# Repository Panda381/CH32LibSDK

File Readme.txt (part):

CH32LibSDK - SDK library for low-end CH32 RISC-V microcontrollers
=================================================================
Pre-alpha version 0.39, under development.

Copyright (c) 2025 Miroslav Nemecek

Panda38@seznam.cz
hardyplotter2@gmail.com
https://github.com/Panda381/CH32LibSDK
https://www.breatharian.eu/hw/ch32libsdk/index_en.html

How to compile on Windows, using command line:

- Use FAR Manager to edit source files and run BAT scripts.
- Download MounRiver Studio v1.92 http://mounriver.com/download
- Install MounRiver Studio. 
- Extract "toolchain\RISC-V Embedded GCC12" compiler to separate folder.
- Edit _c1.bat file and enter path to "bin" folder of the compiler:
   set GCC_CH32_PATH=C:\GCC_CH32\bin
- Extract "toolchain\OpenOCD\bin" tool or use openocd from _tools\openocd.
- Sometimes you may need to use WCH-LinkUtility from the ExTool\SQWTool folder.
  It may sometimes be necessary to erase the flash memory using power-off,
  because OpenOcd cannot do this.
- Compile sample using c.bat.
- Flash compiled sample using e.bat with WCH-LinkE programmer (available here,
  for example: https://pajenicko.cz/usb-programator-a-debug-adapter-wch-link ).
  For the SD card version of the console, simply upload the program to the
  SD card and load it into the processor using the boot loader.
- Clear compilation using d.bat.

AntCalc
-------
AntCalc is a wrist-worn programmable calculator with scientific functions. It
features an inexpensive CH32V002A4M6 processor, a blue-yellow 0.96" I2C OLED
display with an SSD1306 controller and a resolution of 128x64 pixels B&W
(available here, for example:
https://www.hadex.cz/m508c-displej-oled-096-128x64-znaku-iici2c-4piny-modrozluty/).
It also has 12 buttons and is powered by a CR2032 battery. The calculator works
with reverse Polish notation (RPN), which means that numbers are first entered
into the calculator's stack using the Enter button, and then the desired
operation is performed by pressing the operator. The calculator's stack has a
size of 10 registers. The lowest 4 registers are shown on the display under the
names X, Y, Z, and T. The calculator calculates in BCD code with an accuracy of
21 valid digits, along with an exponent in the range of +-99. The display shows
a maximum of 14 digits when displayed without an exponent or 11 digits with an
exponent. Functions are available for calculating direct and inverse
trigonometric functions, power function, decimal and natural logarithmic and
exponential functions. The calculator has 10 memory registers, the contents of
which are stored in flash memory even when the calculator is turned off. The
calculator can be programmed using macros containing a record of keystrokes.
Up to 10 macros, each up to 38 keys long, can be loaded into the calculator's
memory. The calculator measures 30x55 mm. A jumper is used as a switch on the
connector, which is also used to program the processor.

AntCalc calculator functions

The calculator is operated using 12 buttons. 10 buttons are digits, 1 button
is a decimal point, and 1 button is 2nd for switching between modes. In total,
you can switch between 7 states by repeatedly pressing the 2nd button. If an
error occurs during operations (division by zero or square root of a negative
number), the text "overflow" is displayed on the X register row. Pressing any
key will end the error messages and reset the X register.

0..9 ... enter a digit.

. ... Enter a decimal point. If the calculator is in exponent editing mode,
   you can use the decimal point button to return to mantissa editing.

2nd ... Switch between additional calculator functions. The selected mode is
   displayed on the top line of the display on the left.

+, -, *, :, Y^x (2nd 0..4) ... arithmetic operations between registers X and Y

y<>x (2nd 5) ... swap registers X and Y

Vx (2nd 6) ... square root

Enter (2nd 7) ... move number X to register Y

CE (2nd 8) ... Delete the last character during editing. The EE key switches to
   exponent editing, the dot key switches to mantissa editing. The CE key
   activates number editing mode if editing is not in progress.

EE (2nd 9) ... Enter exponent. Use the EE key to start editing the number shown
   on the display. Use the decimal point key to switch to mantissa editing.

+/- (2nd .) ... Change the sign of the mantissa or exponent of the number on
   the display.

sin (2x2nd 0) ... sine

asin (2x2nd 1) ... arc sine

log (2x2nd 2) ... decimal logarithm

ln (2x2nd 3) ... natural logarithm

cos (2x2nd 4) ... cosine

acos (2x2nd 5) ... arccosine

exp10 (2x2nd 6) ... decimal exponent

exp (2x2nd 7) ... natural exponent

tan (2x2nd 8) ... tangent

atan (2x2nd 9) ... arctangent

1/x (2x2nd .) ... reciprocal value

RCL0..RCL9 (3x2nd 0..9) ... recall memory contents 0 to 9

PI (3x2nd .) ... Pi number

STO0..STO9 (4x2nd 0..9) ... Saving a number to memory 0 to 9. The content is
   stored in flash memory even when the device is turned off.

DEG (4x2nd .) ... Switching the angular measure of goniometric functions
   between degrees (DEG) and radians (RAD). The selected setting is displayed
   in the middle of the top line of the display and is stored in flash memory.

RUN0..RUN9 (5x2nd 0..9) ... Play macro number 0 to 9.

INT (5x2nd .) ... Cut off the decimal part of the number (rounding to whole
   numbers towards zero).

PRG0..PRG9 (6x2nd 0..9) ... Start recording a macro into program number 0 to 9.
   The codes of the pressed keys are stored in memory. Up to 38 button codes
   can be stored in one macro. Presses of the 2nd button are not stored in the
   program - the resulting function code is stored as 1 code. During macro
   recording, the text PROG0..PROG9 flashes in the upper right corner of the
   display, indicating that recording is in progress. If the number of buttons
   is exceeded, the indicator remains lit but stops flashing to indicate that
   buttons are no longer being stored. Macro recording can be stopped by
   pressing any of the PRG0 to PRG9 functions (it is not necessary to use the
   same macro number).

C (6x2nd .) ... Clears the calculator's registers. The contents of the memory
   and programs are retained. Turning the calculator off and on has the same
   effect.

Notes on construction:

The calculator uses a very inexpensive Chinese processor CH32V002A4M6. It is
housed in an SOP16 package with large pin spacing, making the calculator's
design suitable even for novice designers. The calculator has two eyelets on
the bottom for attaching a strap. To simplify the design, a jumper plugged into
the connector, which is also used to program the calculator's processor, was
used as a switch. When switched on, the jumper is plugged into the two pins on
the right, and when switched off, it is plugged into the two pins on the left.
A two-color, blue-yellow OLED display with an SSD1306 controller and a
resolution of 128x64 was used. The display is actually monochrome, with the top
16 lines displayed in yellow and the next 48 lines in blue. Alternatively, a
monochrome display can also be used. I leave the design of the top cover with
button labels to other designers  in the prototype, I only used a paper label
with cut-out holes for the buttons.

>>> Source codes and all necessary documentation of the AntCalc calculator can
be found in the CH32LibSDK library in the ch32\DEVICE\ folder.
https://github.com/Panda381/CH32LibSDK/tree/main/ch32/DEVICE <<<

BeatleBoyPad (BeatleBoy, BeatlePad)
-----------------------------------
BeatleBoyPad is dual console with interchangeable ROM cartridges. It consists
of two consoles. The first console, BeatleBoy, contains 128x64 pixel black and
white OLED I2C display with SSD1306 controller, built-in speaker and 6 buttons
(4 directional arrows and A and B buttons). The console is powered by CR2032
battery. The second console, BeatlePad, has black and white output to VGA
monitor and connector for external speaker. Cartridge with program contains
cheap Chinese processor CH32V002J4M6, CH32V003J4M6 or CH32V006F8P6. Note: for
processor V006 different cartridge wiring than for processors V002 and V003 is
used.

The cartridges are common to both consoles. The processor in the cartridge
distinguishes between the two consoles based on the voltage and switches to
the appropriate mode accordingly. Due to the console's auto-detection, it is
therefore necessary to maintain the power supply used - the BeatleBoy console
is powered by a 3V battery, while the BeatlePad console is powered by a 5V
external source. In addition to detecting the supply voltage, the processor
in the BeatlePad console also detects the connection of a VGA cable. The
program in the console will only start after connecting a VGA monitor. This
is so that the cartridge can be reprogrammed in the programmer, as the VGA
console also uses programming pin.

There are 25 games available for the console. All prepared games can be
programmed into all types of cartridges - with V002, V003, or V006 processors.
The V002 processor variant has more RAM available than the V003 processor, and
the output to the VGA monitor is via SPI controller, which allows the use of
higher video mode resolutions (this is not used in the prepared games). The
V006 processor has more RAM than the V002 processor. However, unless required
by the software, it is recommended to use the CH32V003J4M6 processor. Although
this is an older type of processor, its advantage is higher oscillator
stability and therefore less noise in the VGA image.

When constructing the device, it is necessary to use resistors with 1%
accuracy, otherwise button presses may be detected incorrectly. The
brightness of the OLED display is kept low to minimize battery consumption.
The current voltage of the CR2032 battery is displayed when most programs
start. The measurement is performed using the internal reference of the
processor, and therefore the displayed value may vary by up to 10% and
should therefore be taken as a guide only. Pay attention to the pin layout
of the display - there are usually two versions, with the pin order
VCC-GND-SCL-SDA or GND-VDD-SCL-SDA. Both variants are available on the
printed circuit board (alternatively, the display can be connected
interchangeably via a pin header). The OLED display is used here in an
inverted position compared to other consoles - the image rotation is defined
in the display initialization sequence.

An internal HSI RC oscillator is used for VGA image output. Its frequency is
not stabilized by a crystal, so slight signal timing deviations and image
noise must be expected. The V003 processor has slightly lower image noise than
the V002 and V006 processors. Some VGA monitors may not display the image due
to the low quality of the image signal timing.

Programs can be loaded into the cartridge using the WCH-LinkE programmer
(available, for example, here:
https://pajenicko.cz/usb-programator-a-debug-adapter-wch-link). Pin number 4
on the cartridge is left as an option for reprogramming processors requiring
2-wire programming (SWDIO+SWCLK, e.g., CH32X035). Currently, this option is
not used, and it is possible to use this pin as a blind pin to facilitate
cartridge insertion orientation (i.e., cut off pin number 4 on the cartridge
and plug the corresponding pin on the console, e.g., with heat shrink tubing).

BeatleCalc with emulation of Sinclair Scientific and Datamath calculators
-------------------------------------------------------------------------
BeatleCalc is a minimalist scientific calculator, supplemented with emulators
of calculators Sinclair Scientific (1974, TMC0805 processor) and Texas
Instruments TI-2500 Datamath (1972, TMS0803 processor). The calculator uses BCD
code internally, so it does not suffer from the inaccuracies of binary
representation of decimal numbers. It calculates internally with an accuracy
of 13 digits. The exponent ranges from -99 to +99. It includes calculations
of direct and inverse trigonometric functions, in radians and degrees, natural
and decimal logarithmic and exponential functions, powers and roots. It prefers
operation priority, and parentheses can also be used. Numbers can be stored in
4 memory registers, which retain their value even when the power is turned off.

Switching the calculator mode between emulation or BeatleCalc calculator:

- Press and hold the number 1 to 3: 1 selects the default BeatleCalc
  calculator, 2 selects Sinclair Scientific emulation, 3 selects Datamath
  emulation.
- Press the C button briefly. This will reset the calculator.
- Release the number 1 to 3 key. While you hold the key, the selected mode text
  will appear on the display: "CALCUL" is the default BeatleCalc calculator,
  "SINCLAIr" is Sinclair Scientific emulation, and "DATAMATH" is Datamath
  emulation.

Controls for emulated calculators can be found in the relevant calculator
manuals. Please note that the Sinclair calculator uses RPN reverse logic
- you must first enter the number and then the desired operation (typically '+'
is used to insert a number into the stack). Emulators use only some of the
calculator buttons - the layout of the buttons used can be seen in the pictures
of the calculator labels.

BeatleCalc calculator functions:

STO1..STO4 ... Stores the number on the display in memory registers 1 to 4.
   The number is stored in the flash memory of the second CPU2 processor and
   remains available even after the power is turned off.

RCL1..RCL4 ... Displaying a number from memory registers 1 to 4.

CE ... Clearing the last digit or turning off the error indicator. If an
   unedited number is displayed, the calculator switches to edit mode.

2nd, 3rd ... Selection of alternative functions. An indicator appears at the
   first position on the display (2nd=upper line, 3rd=lower line).

= ... Calculation of the expression. Repeated pressing repeats the last
   operation with the last operand.

EE ... Exponent input mode. If an unedited number is displayed, the calculator
   enters exponent edit mode. Press the decimal point key to enter mantissa
   edit mode.

LOG, EXP10 ... Logarithmic and exponential functions with a decimal base.

LN, EXP ... Logarithmic and exponential functions with a natural base.

TAN, ATAN, SIN, ASIN, COS, ACOS ... Trigonometric functions calculated in
   radians.

TAND, ATAND, SIND, ASIND, COSD, ACOSD ... Trigonometric functions calculated
   in degrees.

Notes on construction:

Two CH32V002A4M6 processors were used in the calculator. The reason for this
choice (apart from the low price) is that they are easy to solder, which is
also suitable for beginners. The CPU1 processor is the main processing unit.
The CPU2 processor controls the display multiplexer and is used to store the
configuration and memory registers. The photos show a prototype of the
calculator  I focused primarily on the calculator software, not the design,
so I recommend choosing your own calculator design. A printed circuit board can
be used as the top cover of the calculator. For the prototype, I printed the
label on paper, covered it with transparent adhesive tape on both sides, and
cut out the holes for the buttons with a skin punch. I recommend covering the
display with red Plexiglas, otherwise it may be difficult to read in bright
light. The capacitors should be soldered horizontally so that they do not
interfere with the top cover. I used a 1-digit LED display as the digit in the
first position. You do not have to use it, because only the sign of the number
and the indicators for the 2nd and 3rd buttons (segments A, D, and G) are
displayed in this position. You can replace the digit display with a flat red
LED connected between signals D1 and SG. The 2nd and 3rd indicators are not
necessary. I did not solve the power supply issue in the prototype. It is also
possible to use, for example, a 3.7V battery with a charging circuit. A CR2032
battery may not be powerful enough, as the display may have a high power
consumption.

The calculator firmware consists of two parts. In the ch32\DEVICE\BeatleCalc
folder, you will find the main executive firmware, which you will upload to the
CPU1 processor (e.g., using the WCH-LinkE programmer:
https://pajenicko.cz/usb-programator-a-debug-adapter-wch-link).
The ch32\DEVICE\BeatleCalc_CPU2 folder contains the firmware for the second
processor, CPU2. Until the firmware is loaded into both processors and
communication between them is working, the display will remain dark. If you
need to find a malfunction, use the ch32\DEMO\LED program, in which you will
enter the appropriate pins and use the control LED to check whether the signals
are OK.

Note: Calculator emulation was verified using the emulator
https://static.righto.com/calculator/sinclair_scientific_simulator.html by
Ken Shirriff. No physical calculators were available to verify functionality,
so it is possible that the calculators' functions may not correspond exactly
to the original.

>>> Source codes and all necessary documentation can be found in the CH32LibSDK
  library in the ch32\DEVICE\ folder. <<<

BabyBoy
-------
BabyBoy is the simplest game mini-console with 6 buttons, an inexpensive
CH32V002A4M6 processor (price 10 cents), a built-in speaker, and 128x64 pixel
black-and-white OLED I2C display with an SSD1306 controller. The console is
powered by a CR2032 battery, or it can be powered by an external 3.3V source
via the programming connector. Thanks to simplifications and the easy soldering
of the processor in the SOP16 package with a pin pitch of 1.27mm, the console
is primarily intended for beginners as a kit for their first introduction to
electronics.

Pay attention to the pin layout on the display  there are usually two
versions, with the pin order VCC-GND-SCL-SDA or GND-VDD-SCL-SDA. I used two pin
headers on the circuit board for both display versions so that I could change
the displays and insert them into the correct position.

BabyBoy does not include an SD card. Programs must be uploaded to the processor
using the WCH-LinkE programmer (available here, for example:
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
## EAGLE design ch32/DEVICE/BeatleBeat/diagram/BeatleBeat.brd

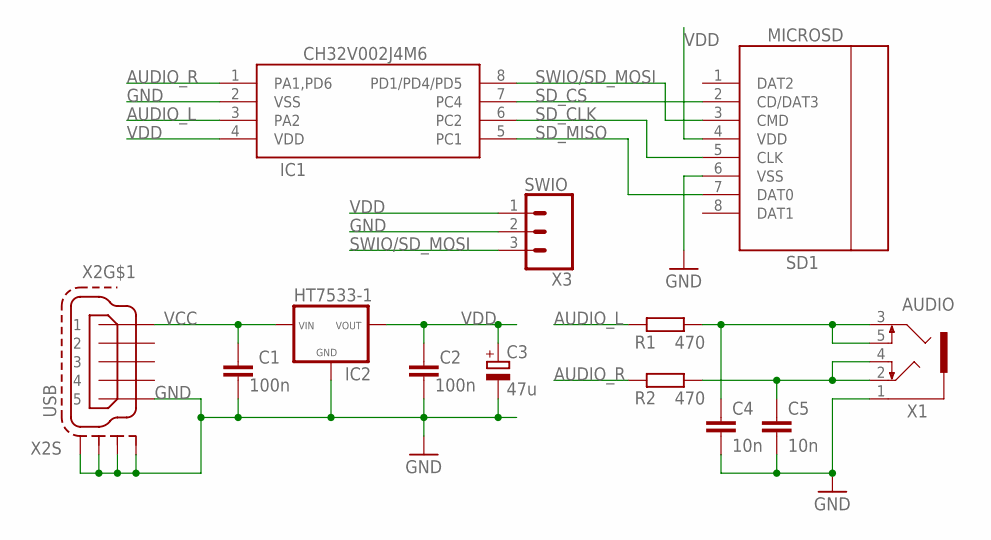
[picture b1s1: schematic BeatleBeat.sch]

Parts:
C1, C2: 100n; C1206K
C3: 47u; C/6032-28R
C4, C5: 10n; C1206K
IC1: CH32V002J4M6; SOP8
IC2: HT7533-1
R1, R2: 470; M1206
SD1: MICROSD
X1: AUDIO; 1503_09
X2: USB; 32005-201
X3: SWIO; 1X03_LONGPADS

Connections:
AUDIO_L: IC1.3 (PA2), R1.2
AUDIO_R: IC1.1 (PA1,PD6), R2.2
GND: C1.2, C2.2, C3.-, C4.2, C5.2, IC1.2 (VSS), IC2.GND, SD1.6 (VSS), X1.1, X2.5, X2.M1 (S1), X2.M2 (S2), X2.M3 (S3), X2.M4 (S4), X3.2
unnamed: C4.1, R1.1, X1.3, X1.5
unnamed: C5.1, R2.1, X1.2, X1.4
SD_CLK: IC1.6 (PC2), SD1.5 (CLK)
SD_CS: IC1.7 (PC4), SD1.2 (CD/DAT3)
SD_MISO: IC1.5 (PC1), SD1.7 (DAT0)
SWIO/SD_MOSI: IC1.8 (PD1/PD4/PD5), SD1.3 (CMD), X3.3
VCC: C1.1, IC2.VIN, X2.1
VDD: C2.1, C3.+, IC1.4 (VDD), IC2.VOUT, SD1.4 (VDD), X3.1

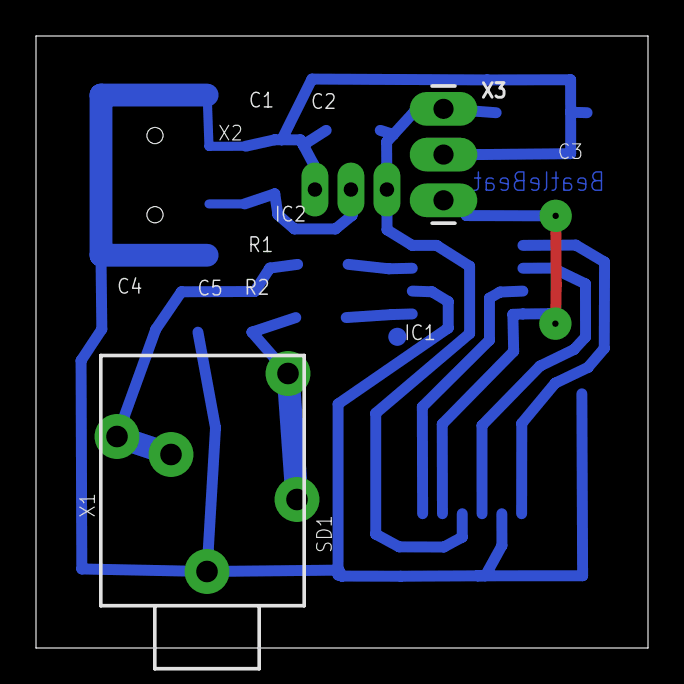
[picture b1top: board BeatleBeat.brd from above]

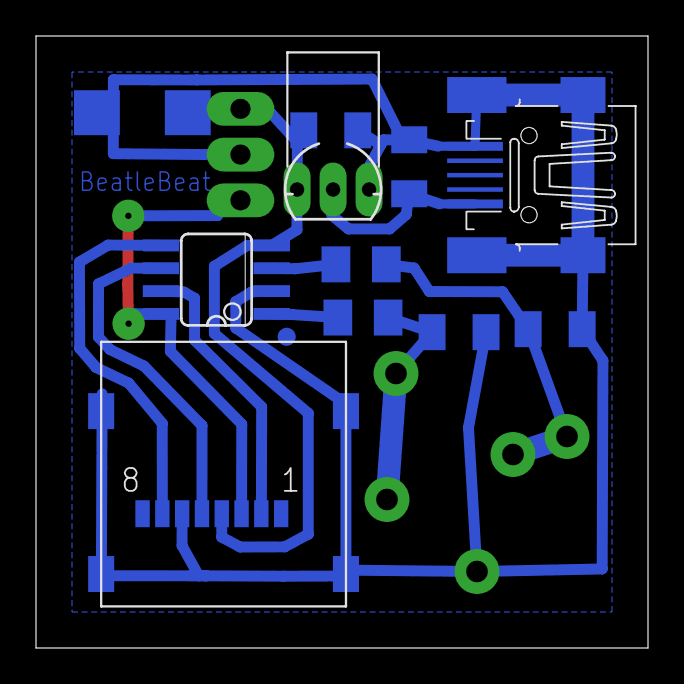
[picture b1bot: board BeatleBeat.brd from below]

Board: 2 copper layers, 34.0 x 34.0 mm, 13 parts (11 on the bottom side), 11 nets.

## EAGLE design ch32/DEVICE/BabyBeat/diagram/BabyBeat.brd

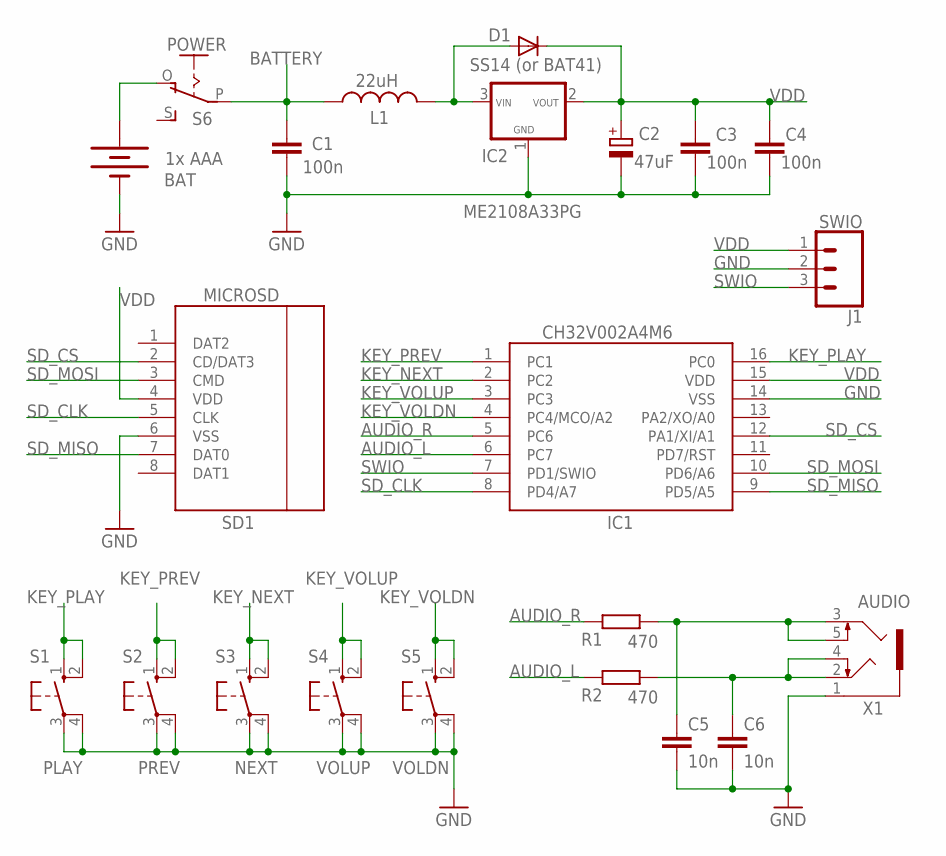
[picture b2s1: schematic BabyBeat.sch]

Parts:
BAT: 1x AAA; BATTERY-AAA-KIT
C1, C3, C4: 100n; C1206K
C2: 47uF; 140CLH-0810
C5, C6: 10n; C1206K
D1: SS14 (or BAT41); SOD-123_MINI-SMA
IC1: CH32V002A4M6; SOP16
IC2: ME2108A33PG; SOT89-R
J1: SWIO; 1X03_LONGPADS
L1: 22uH; POWER-CHOKE_WE-TPC
R1, R2: 470; M1206
S1: PLAY; B3F-10XX
S2: PREV; B3F-10XX
S3: NEXT; B3F-10XX
S4: VOLUP; B3F-10XX
S5: VOLDN; B3F-10XX
S6: POWER; EG1218
SD1: MICROSD
X1: AUDIO; 1503_09

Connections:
AUDIO_L: IC1.6 (PC7), R2.2
AUDIO_R: IC1.5 (PC6), R1.2
BATTERY: C1.1, L1.1, S6.P
GND: BAT.GND@1 (-), C1.2, C2.-, C3.2, C4.2, C5.2, C6.2, IC1.14 (VSS), IC2.1 (GND), J1.2, S1.3, S1.4 (P1), S2.3, S2.4 (P1), S3.3, S3.4 (P1), S4.3, S4.4 (P1), S5.3, S5.4 (P1), SD1.6 (VSS), X1.1
KEY_NEXT: IC1.2 (PC2), S3.1 (S), S3.2 (S1)
KEY_PLAY: IC1.16 (PC0), S1.1 (S), S1.2 (S1)
KEY_PREV: IC1.1 (PC1), S2.1 (S), S2.2 (S1)
KEY_VOLDN: IC1.4 (PC4/MCO/A2), S5.1 (S), S5.2 (S1)
KEY_VOLUP: IC1.3 (PC3), S4.1 (S), S4.2 (S1)
unnamed: C5.1, R1.1, X1.3, X1.5
unnamed: BAT.PWR@1 (+), S6.O
unnamed: D1.A, IC2.3 (IN), L1.2
unnamed: C6.1, R2.1, X1.2, X1.4
SD_CLK: IC1.8 (PD4/A7), SD1.5 (CLK)
SD_CS: IC1.12 (PA1/XI/A1), SD1.2 (CD/DAT3)
SD_MISO: IC1.9 (PD5/A5), SD1.7 (DAT0)
SD_MOSI: IC1.10 (PD6/A6), SD1.3 (CMD)
SWIO: IC1.7 (PD1/SWIO), J1.3
VDD: C2.+, C3.1, C4.1, D1.C, IC1.15 (VDD), IC2.2 (VOUT), J1.1, SD1.4 (VDD)

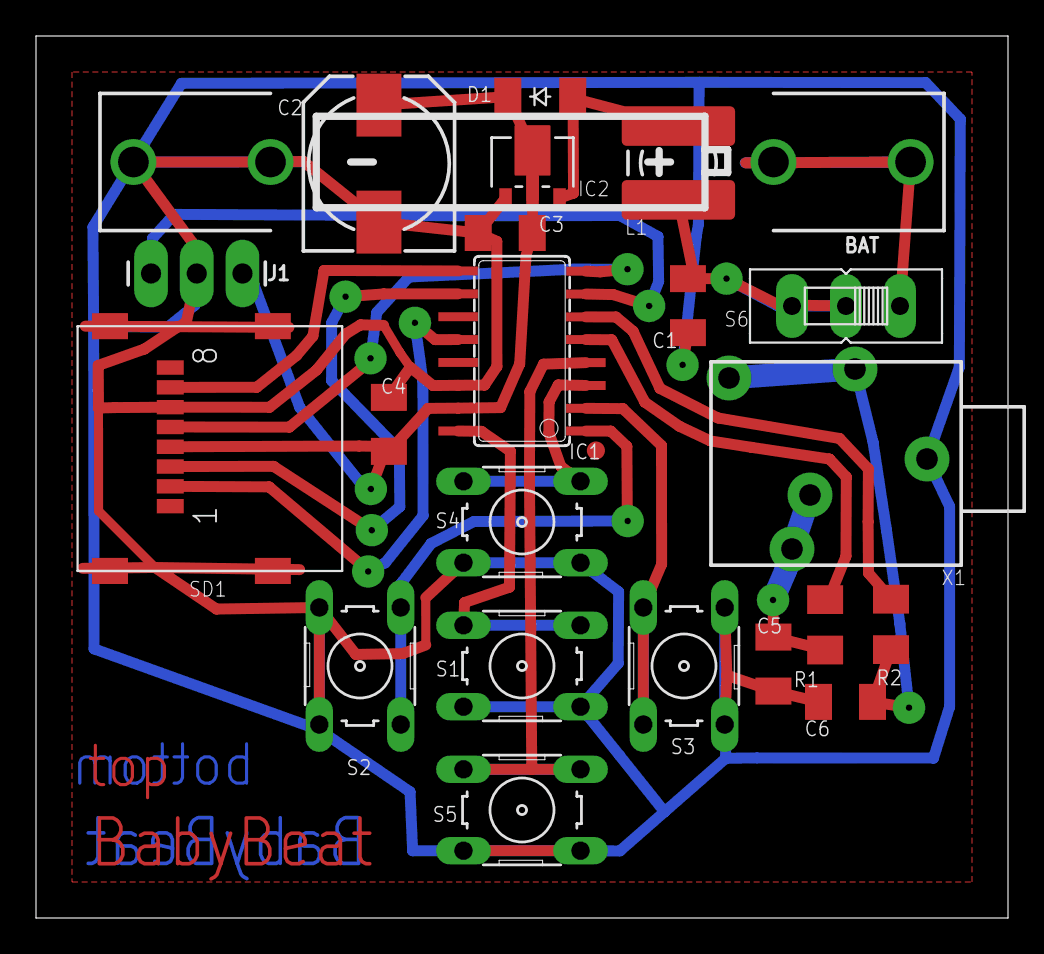
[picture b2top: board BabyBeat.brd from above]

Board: 2 copper layers, 54.0 x 49.0 mm, 22 parts (0 on the bottom side), 19 nets.

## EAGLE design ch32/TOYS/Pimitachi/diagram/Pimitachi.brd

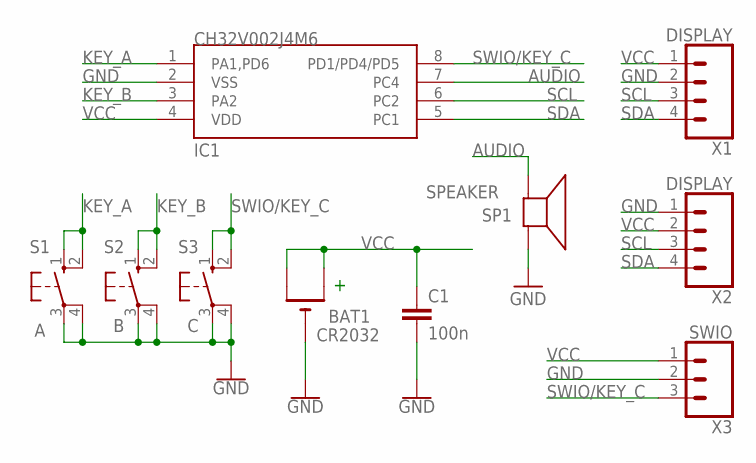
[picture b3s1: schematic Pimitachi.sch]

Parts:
BAT1: CR2032; CR2032-THRU
C1: 100n; C1206K
IC1: CH32V002J4M6; SOP8
S1: A; B3F-10XX
S2: B; B3F-10XX
S3: C; B3F-10XX
SP1: SPEAKER; SPEAKER-PIEZO
X1, X2: DISPLAY; 1X04
X3: SWIO; 1X03_SMD_RA_MALE_POST_SMALLEST

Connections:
AUDIO: IC1.7 (PC4), SP1.1 (+)
GND: BAT1.-, C1.2, IC1.2 (VSS), S1.3, S1.4 (P1), S2.3, S2.4 (P1), S3.3, S3.4 (P1), SP1.2 (-), X1.2, X2.1, X3.2
KEY_A: IC1.1 (PA1,PD6), S1.1 (S), S1.2 (S1)
KEY_B: IC1.3 (PA2), S2.1 (S), S2.2 (S1)
SCL: IC1.6 (PC2), X1.3, X2.3
SDA: IC1.5 (PC1), X1.4, X2.4
SWIO/KEY_C: IC1.8 (PD1/PD4/PD5), S3.1 (S), S3.2 (S1), X3.3
VCC: BAT1.+1 (+), BAT1.+2 (+1), C1.1, IC1.4 (VDD), X1.1, X2.2, X3.1

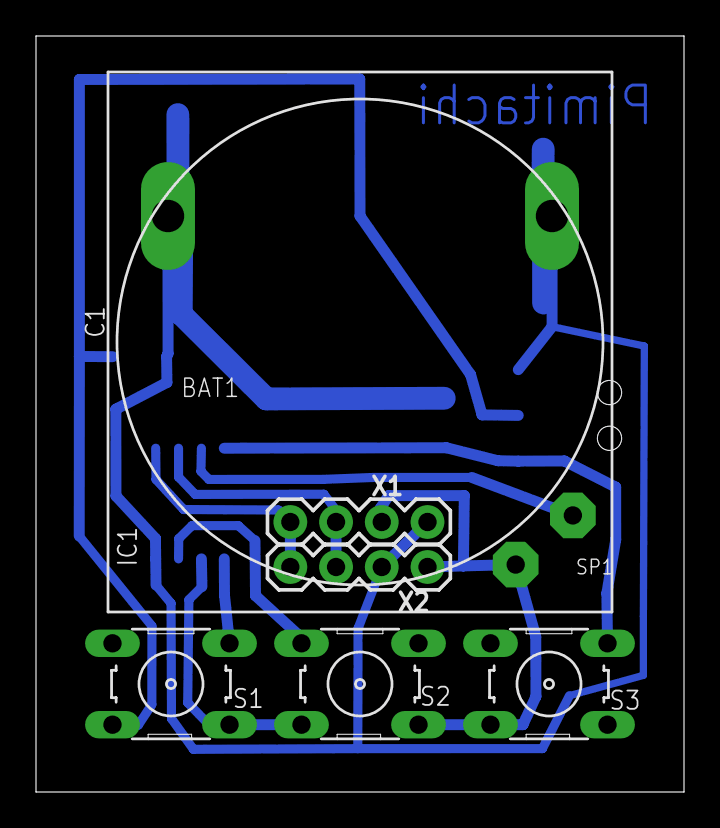
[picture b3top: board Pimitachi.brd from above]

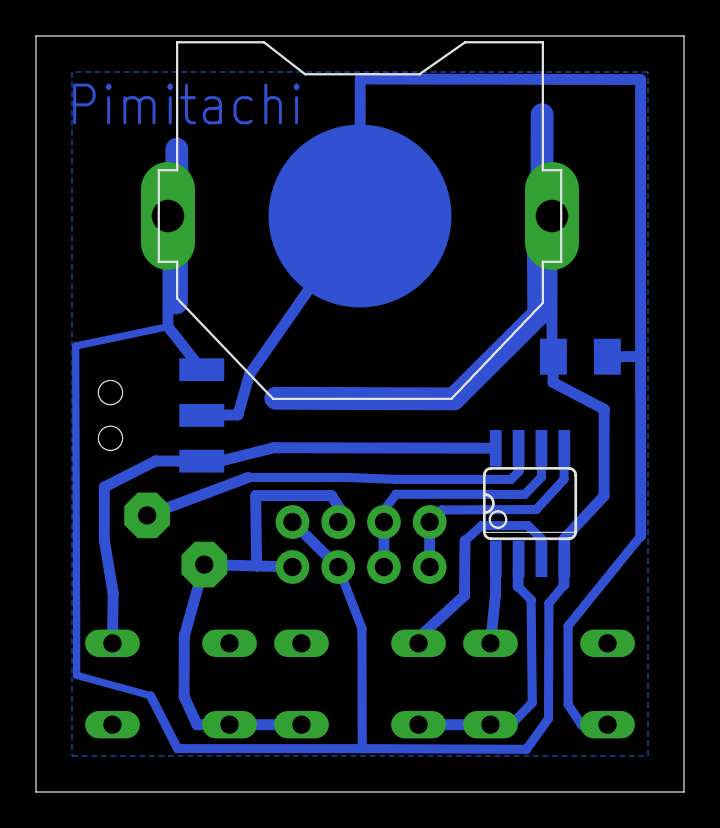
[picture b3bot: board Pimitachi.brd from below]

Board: 2 copper layers, 36.0 x 42.0 mm, 10 parts (4 on the bottom side), 8 nets.

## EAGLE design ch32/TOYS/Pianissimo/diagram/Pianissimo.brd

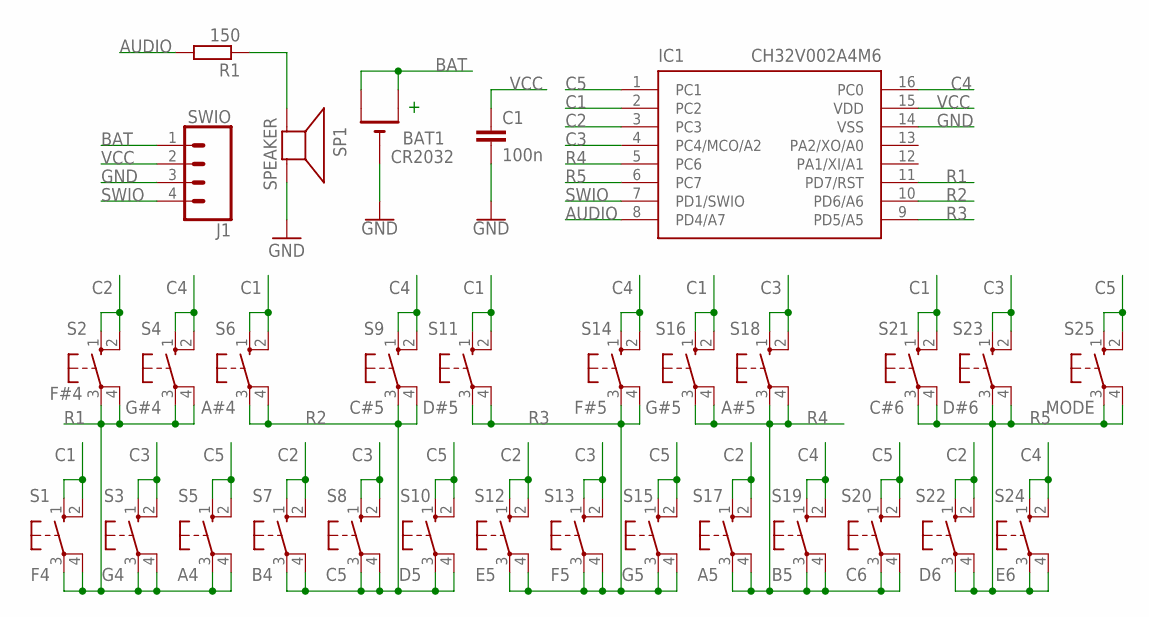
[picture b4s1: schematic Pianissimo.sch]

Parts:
BAT1: CR2032; CR2032-THRU
C1: 100n; C050-024X044
IC1: CH32V002A4M6; SOP16
J1: SWIO; 1X04_LONGPADS
R1: 150; 0204/7
S1: F4; B3F-10XX
S2: F#4; B3F-10XX
S3: G4; B3F-10XX
S4: G#4; B3F-10XX
S5: A4; B3F-10XX
S6: A#4; B3F-10XX
S7: B4; B3F-10XX
S8: C5; B3F-10XX
S9: C#5; B3F-10XX
S10: D5; B3F-10XX
S11: D#5; B3F-10XX
S12: E5; B3F-10XX
S13: F5; B3F-10XX
S14: F#5; B3F-10XX
S15: G5; B3F-10XX
S16: G#5; B3F-10XX
S17: A5; B3F-10XX
S18: A#5; B3F-10XX
S19: B5; B3F-10XX
S20: C6; B3F-10XX
S21: C#6; B3F-10XX
S22: D6; B3F-10XX
S23: D#6; B3F-10XX
S24: E6; B3F-10XX
S25: MODE; B3F-10XX
SP1: SPEAKER; AL60P

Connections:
AUDIO: IC1.8 (PD4/A7), R1.2
BAT: BAT1.+1 (+), BAT1.+2 (+1), J1.1
C1: IC1.2 (PC2), S1.1 (S), S1.2 (S1), S6.1 (S), S6.2 (S1), S11.1 (S), S11.2 (S1), S16.1 (S), S16.2 (S1), S21.1 (S), S21.2 (S1)
C2: IC1.3 (PC3), S2.1 (S), S2.2 (S1), S7.1 (S), S7.2 (S1), S12.1 (S), S12.2 (S1), S17.1 (S), S17.2 (S1), S22.1 (S), S22.2 (S1)
C3: IC1.4 (PC4/MCO/A2), S3.1 (S), S3.2 (S1), S8.1 (S), S8.2 (S1), S13.1 (S), S13.2 (S1), S18.1 (S), S18.2 (S1), S23.1 (S), S23.2 (S1)
C4: IC1.16 (PC0), S4.1 (S), S4.2 (S1), S9.1 (S), S9.2 (S1), S14.1 (S), S14.2 (S1), S19.1 (S), S19.2 (S1), S24.1 (S), S24.2 (S1)
C5: IC1.1 (PC1), S5.1 (S), S5.2 (S1), S10.1 (S), S10.2 (S1), S15.1 (S), S15.2 (S1), S20.1 (S), S20.2 (S1), S25.1 (S), S25.2 (S1)
GND: BAT1.-, C1.2, IC1.14 (VSS), J1.3, SP1.2 (-)
unnamed: R1.1, SP1.1 (+)
R1: IC1.11 (PD7/RST), S1.3, S1.4 (P1), S2.3, S2.4 (P1), S3.3, S3.4 (P1), S4.3, S4.4 (P1), S5.3, S5.4 (P1)
R2: IC1.10 (PD6/A6), S6.3, S6.4 (P1), S7.3, S7.4 (P1), S8.3, S8.4 (P1), S9.3, S9.4 (P1), S10.3, S10.4 (P1)
R3: IC1.9 (PD5/A5), S11.3, S11.4 (P1), S12.3, S12.4 (P1), S13.3, S13.4 (P1), S14.3, S14.4 (P1), S15.3, S15.4 (P1)
R4: IC1.5 (PC6), S16.3, S16.4 (P1), S17.3, S17.4 (P1), S18.3, S18.4 (P1), S19.3, S19.4 (P1), S20.3, S20.4 (P1)
R5: IC1.6 (PC7), S21.3, S21.4 (P1), S22.3, S22.4 (P1), S23.3, S23.4 (P1), S24.3, S24.4 (P1), S25.3, S25.4 (P1)
SWIO: IC1.7 (PD1/SWIO), J1.4
VCC: C1.1, IC1.15 (VDD), J1.2

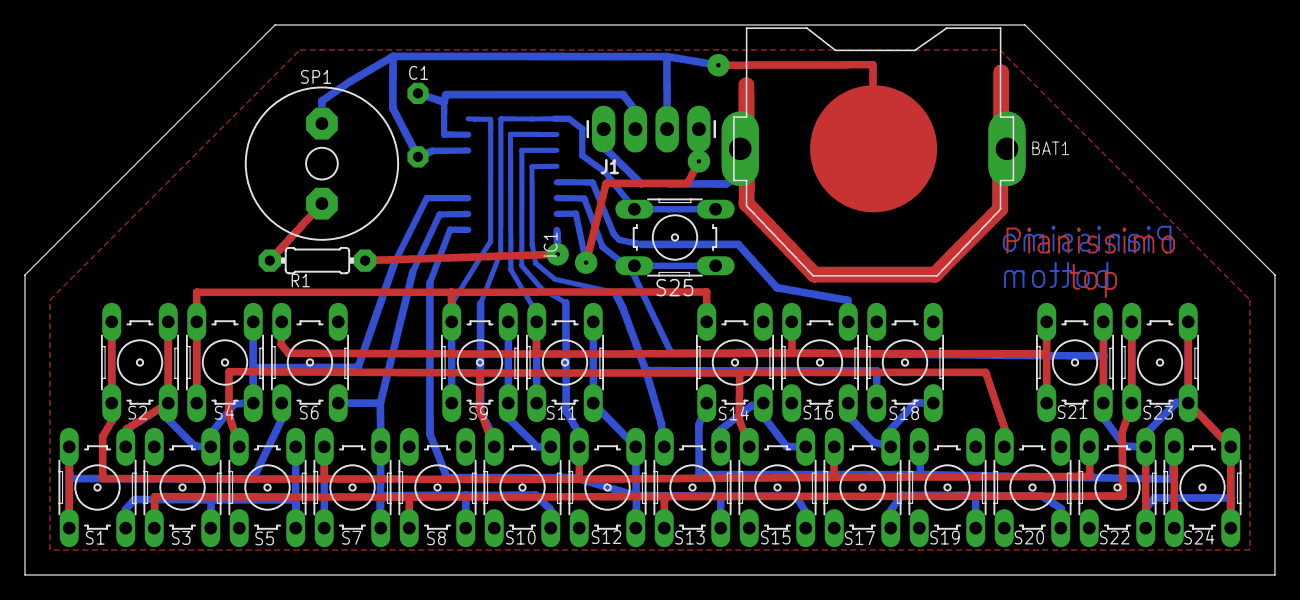
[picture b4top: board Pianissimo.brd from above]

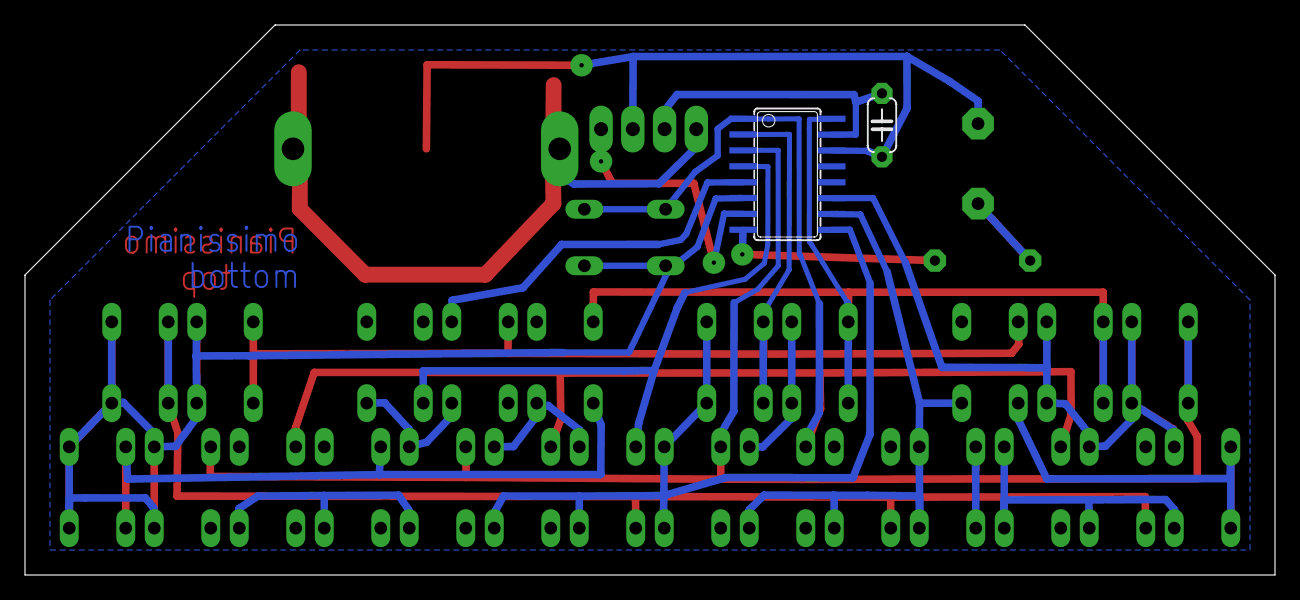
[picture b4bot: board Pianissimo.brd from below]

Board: 2 copper layers, 100.0 x 44.0 mm, 31 parts (2 on the bottom side), 16 nets.

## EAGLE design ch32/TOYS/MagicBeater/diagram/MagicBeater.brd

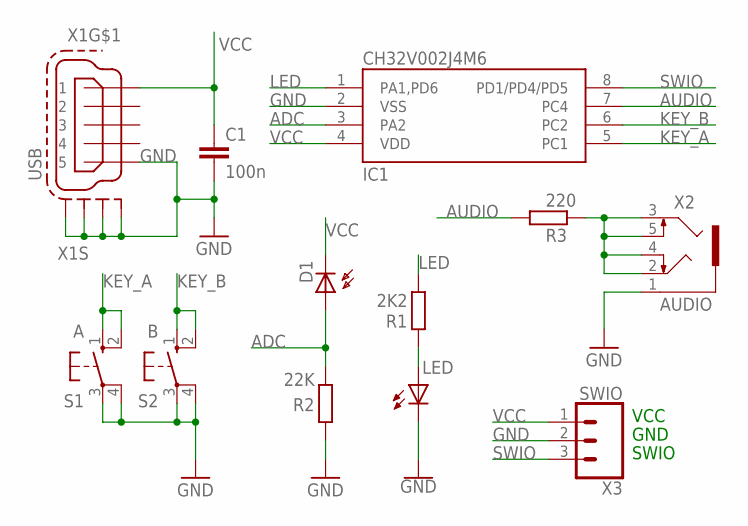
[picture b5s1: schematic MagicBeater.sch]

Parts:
C1: 100n; C050-024X044
D1: BPW32
IC1: CH32V002J4M6; SOP8
LED: LEDLED5MMB; LED5MMB
R1: 2K2; 0204/7
R2: 22K; 0204/7
R3: 220; 0204/7
S1: A; B3F-10XX
S2: B; B3F-10XX
X1: USB; 32005-201
X2: AUDIO; 1503_09
X3: SWIO; 1X03_LONGPADS

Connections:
ADC: D1.A, IC1.3 (PA2), R2.1
AUDIO: IC1.7 (PC4), R3.2
GND: C1.2, IC1.2 (VSS), LED.K (C), R2.2, S1.3, S1.4 (P1), S2.3, S2.4 (P1), X1.5, X1.M1 (S1), X1.M2 (S2), X1.M3 (S3), X1.M4 (S4), X2.1, X3.2
KEY_A: IC1.5 (PC1), S1.1 (S), S1.2 (S1)
KEY_B: IC1.6 (PC2), S2.1 (S), S2.2 (S1)
LED: IC1.1 (PA1,PD6), R1.1
unnamed: LED.A, R1.2
unnamed: R3.1, X2.2, X2.3, X2.4, X2.5
SWIO: IC1.8 (PD1/PD4/PD5), X3.3
VCC: C1.1, D1.K (C), IC1.4 (VDD), X1.1, X3.1

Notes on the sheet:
VCC
GND
SWIO

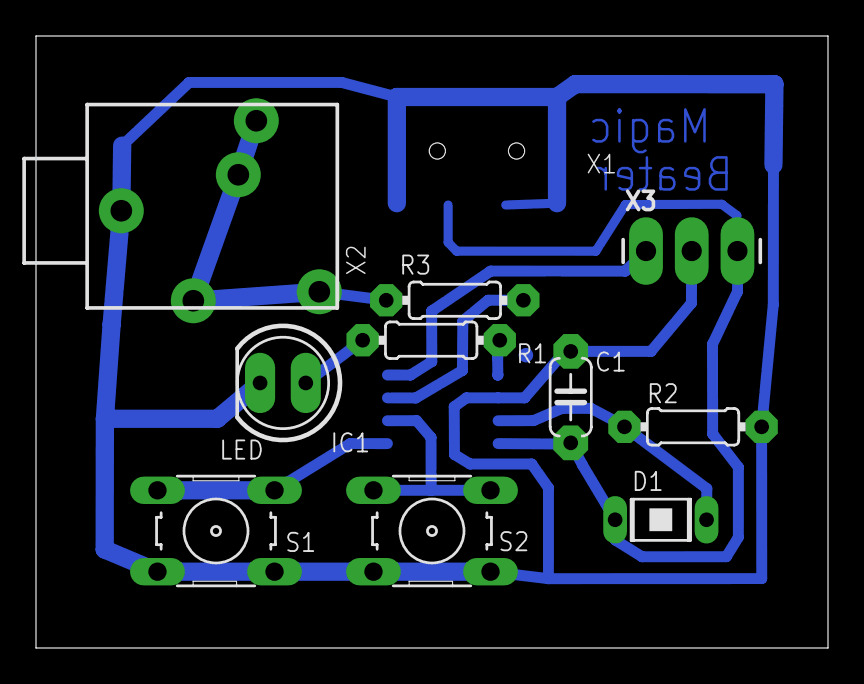
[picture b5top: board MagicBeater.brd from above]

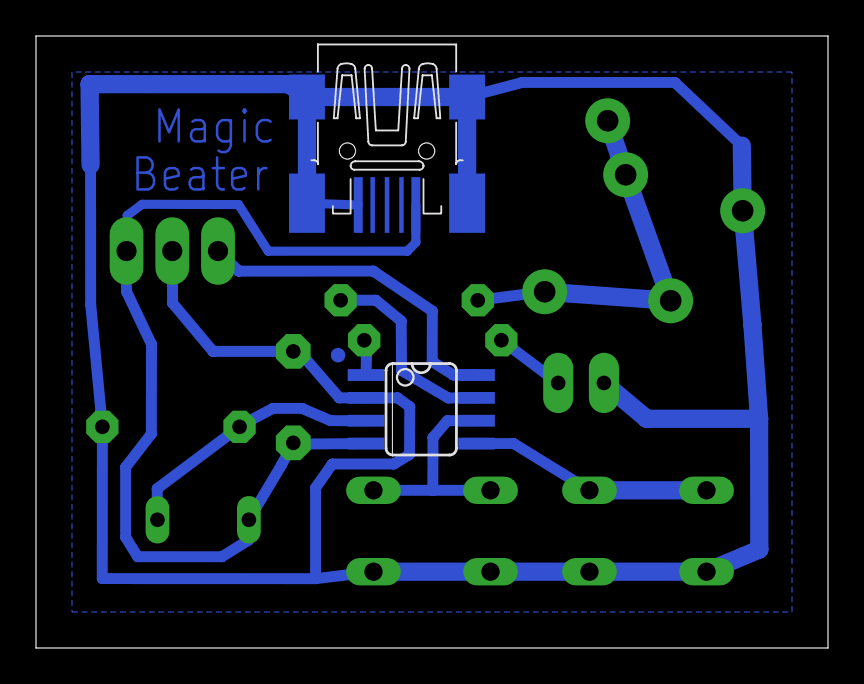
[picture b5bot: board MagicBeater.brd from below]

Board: 2 copper layers, 44.0 x 34.0 mm, 12 parts (2 on the bottom side), 10 nets.

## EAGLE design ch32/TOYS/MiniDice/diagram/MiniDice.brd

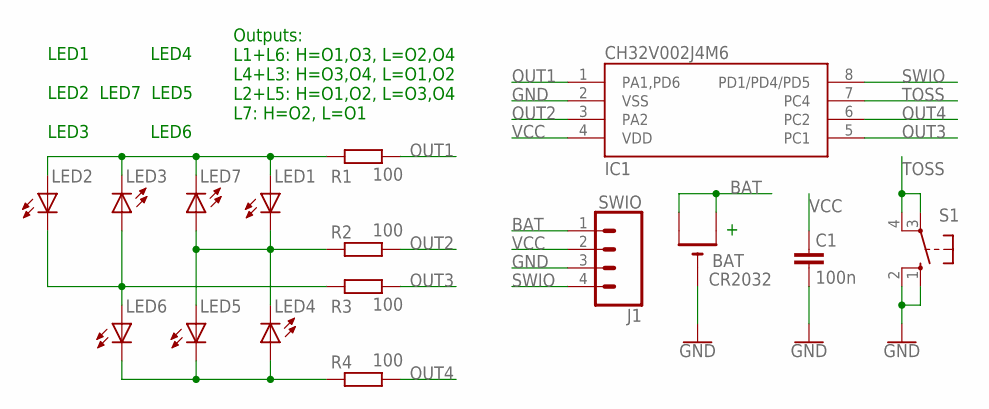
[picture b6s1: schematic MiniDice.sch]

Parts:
BAT: CR2032; CR2032-SMD
C1: 100n; C1206K
IC1: CH32V002J4M6; SOP8
J1: SWIO; 1X04_SMD_LONG
LED1, LED2, LED3, LED4, LED5, LED6, LED7: LEDLED5MMB; LED5MMB
R1, R2, R3, R4: 100; M1206
S1: 10-XXB3F-10XXSMD; B3F-10XXSMD

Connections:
BAT: BAT.+$1 (+), BAT.+$2 (+1), J1.1
GND: BAT.-, C1.2, IC1.2 (VSS), J1.3, S1.1 (S), S1.2 (S1)
unnamed: LED4.A, LED5.K (C), LED6.K (C), R4.2
unnamed: LED1.A, LED2.A, LED3.K (C), LED7.K (C), R1.1
unnamed: LED1.K (C), LED4.K (C), LED5.A, LED7.A, R2.2
unnamed: LED2.K (C), LED3.A, LED6.A, R3.2
OUT1: IC1.1 (PA1,PD6), R1.2
OUT2: IC1.3 (PA2), R2.1
OUT3: IC1.5 (PC1), R3.1
OUT4: IC1.6 (PC2), R4.1
SWIO: IC1.8 (PD1/PD4/PD5), J1.4
TOSS: IC1.7 (PC4), S1.3, S1.4 (P1)
VCC: C1.1, IC1.4 (VDD), J1.2

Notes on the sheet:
LED1 LED4 LED2 LED7 LED5 LED3 LED6
Outputs: L1+L6: H=O1,O3, L=O2,O4 L4+L3: H=O3,O4, L=O1,O2 L2+L5: H=O1,O2, L=O3,O4 L7: H=O2, L=O1

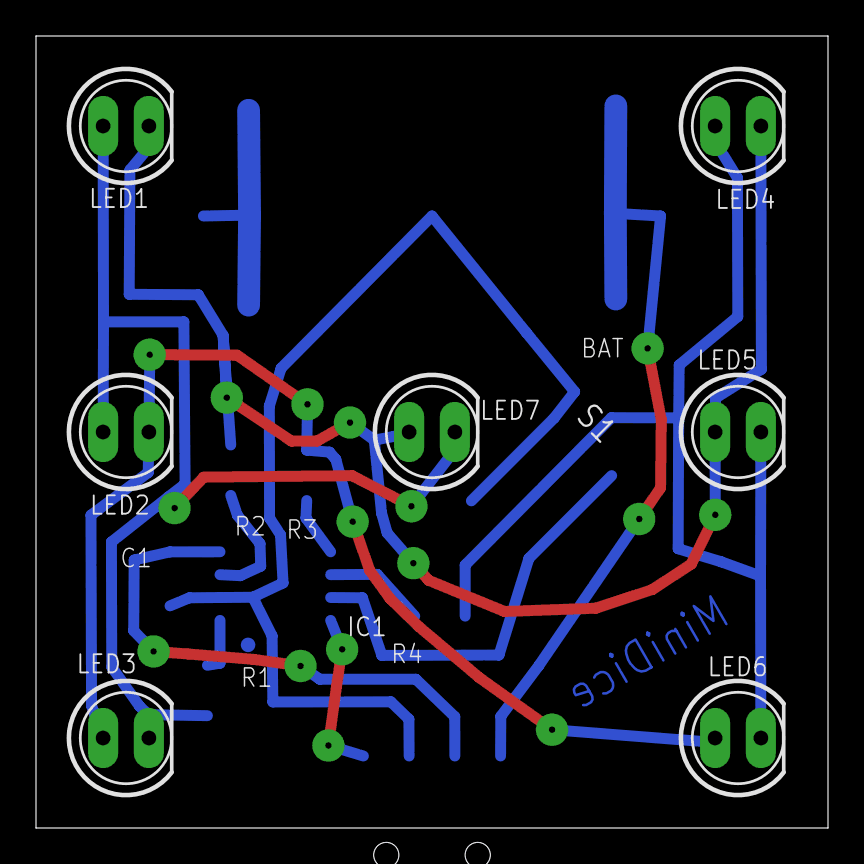
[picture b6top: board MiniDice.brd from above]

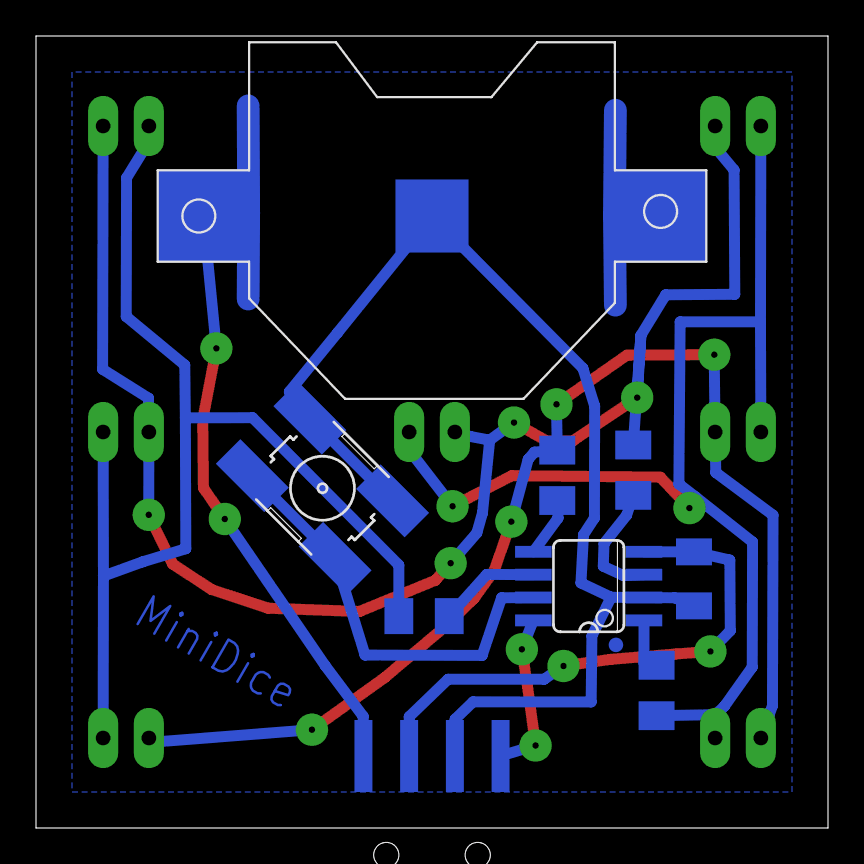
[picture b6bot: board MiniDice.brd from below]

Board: 2 copper layers, 44.0 x 44.0 mm, 16 parts (9 on the bottom side), 13 nets.

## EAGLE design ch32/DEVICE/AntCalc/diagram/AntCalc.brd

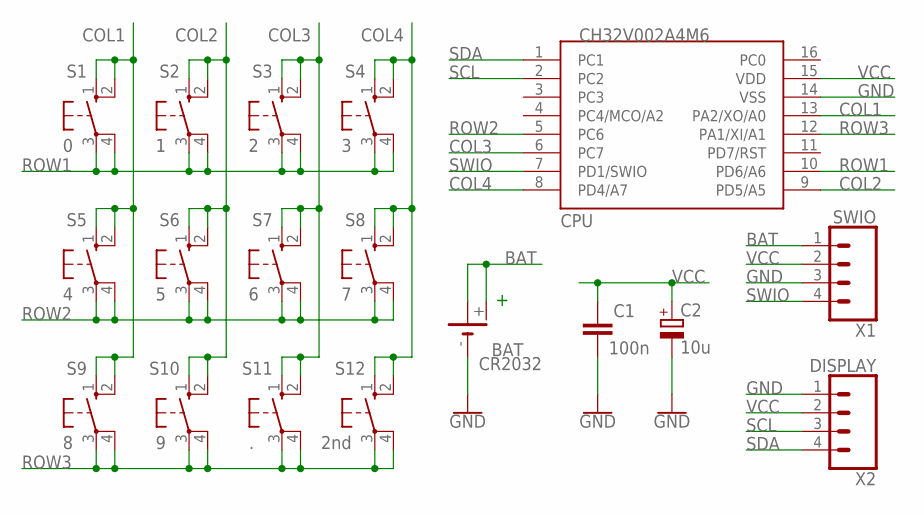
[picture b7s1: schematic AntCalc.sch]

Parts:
BAT: CR2032; CR2032H
C1: 100n; C0805K
C2: 10u; PANASONIC_B
CPU: CH32V002A4M6; SOP16
S1: 0; B3F-10XXC
S2: 1; B3F-10XXC
S3: 2; B3F-10XXC
S4: 3; B3F-10XXC
S5: 4; B3F-10XXC
S6: 5; B3F-10XXC
S7: 6; B3F-10XXC
S8: 7; B3F-10XXC
S9: 8; B3F-10XXC
S10: 9; B3F-10XXC
S11: .; B3F-10XXC
S12: 2nd; B3F-10XXC
X1: SWIO; 1X04_LONGPADS
X2: DISPLAY; 1X04

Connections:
BAT: BAT.+, BAT.+@1 (+), X1.1
COL1: CPU.13 (PA2/XO/A0), S1.1 (S), S1.2 (S1), S5.1 (S), S5.2 (S1), S9.1 (S), S9.2 (S1)
COL2: CPU.9 (PD5/A5), S2.1 (S), S2.2 (S1), S6.1 (S), S6.2 (S1), S10.1 (S), S10.2 (S1)
COL3: CPU.6 (PC7), S3.1 (S), S3.2 (S1), S7.1 (S), S7.2 (S1), S11.1 (S), S11.2 (S1)
COL4: CPU.8 (PD4/A7), S4.1 (S), S4.2 (S1), S8.1 (S), S8.2 (S1), S12.1 (S), S12.2 (S1)
GND: BAT.-, C1.2, C2.-, CPU.14 (VSS), X1.3, X2.1
ROW1: CPU.10 (PD6/A6), S1.3, S1.4 (P1), S2.3, S2.4 (P1), S3.3, S3.4 (P1), S4.3, S4.4 (P1)
ROW2: CPU.5 (PC6), S5.3, S5.4 (P1), S6.3, S6.4 (P1), S7.3, S7.4 (P1), S8.3, S8.4 (P1)
ROW3: CPU.12 (PA1/XI/A1), S9.3, S9.4 (P1), S10.3, S10.4 (P1), S11.3, S11.4 (P1), S12.3, S12.4 (P1)
SCL: CPU.2 (PC2), X2.3
SDA: CPU.1 (PC1), X2.4
SWIO: CPU.7 (PD1/SWIO), X1.4
VCC: C1.1, C2.+, CPU.15 (VDD), X1.2, X2.2

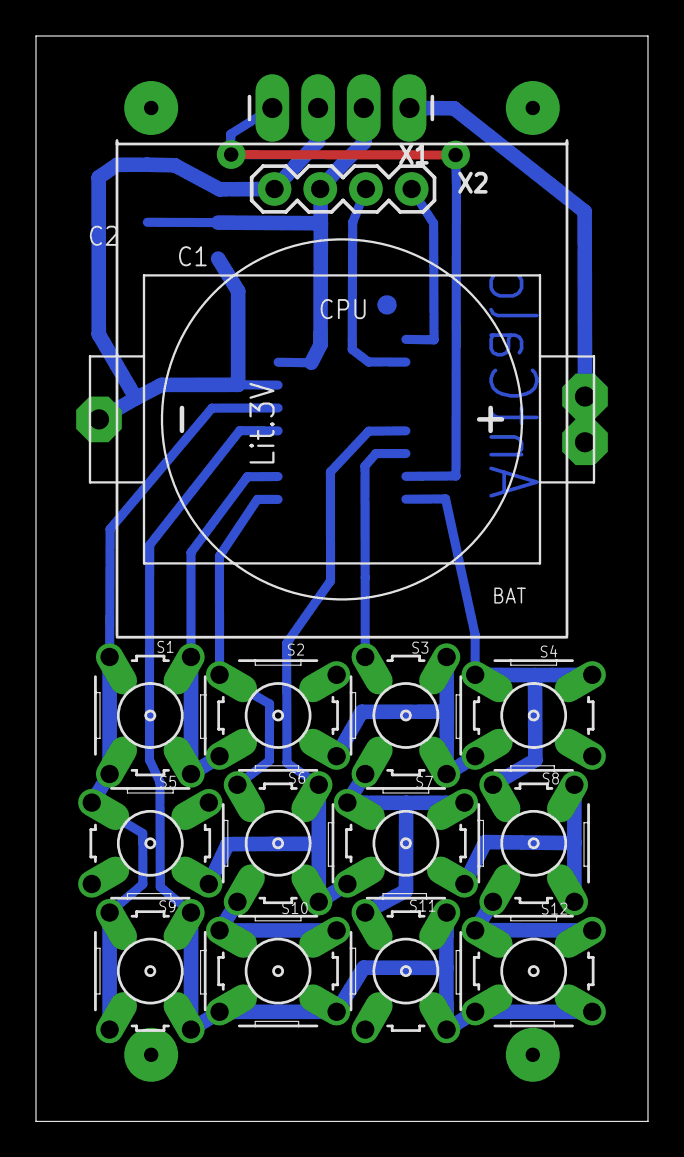
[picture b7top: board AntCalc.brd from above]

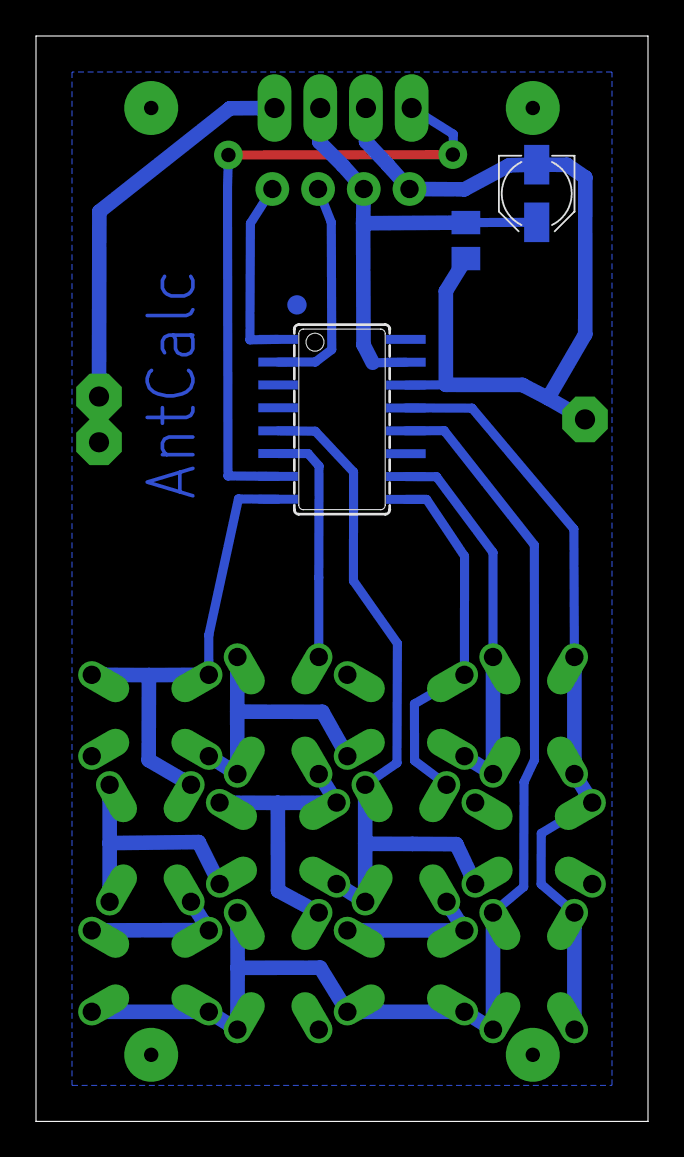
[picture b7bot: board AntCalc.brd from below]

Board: 2 copper layers, 34.0 x 60.3 mm, 18 parts (3 on the bottom side), 13 nets.

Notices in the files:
parts and their libraries:
SparkFun-Connectors: Licensing: Creative Commons ShareAlike 4.0 International - https://creativecommons.org/licenses/by-sa/4.0
Wuerth_Elektronik_eiCan_Communication_Co: Copyright: Würth Elektronik
